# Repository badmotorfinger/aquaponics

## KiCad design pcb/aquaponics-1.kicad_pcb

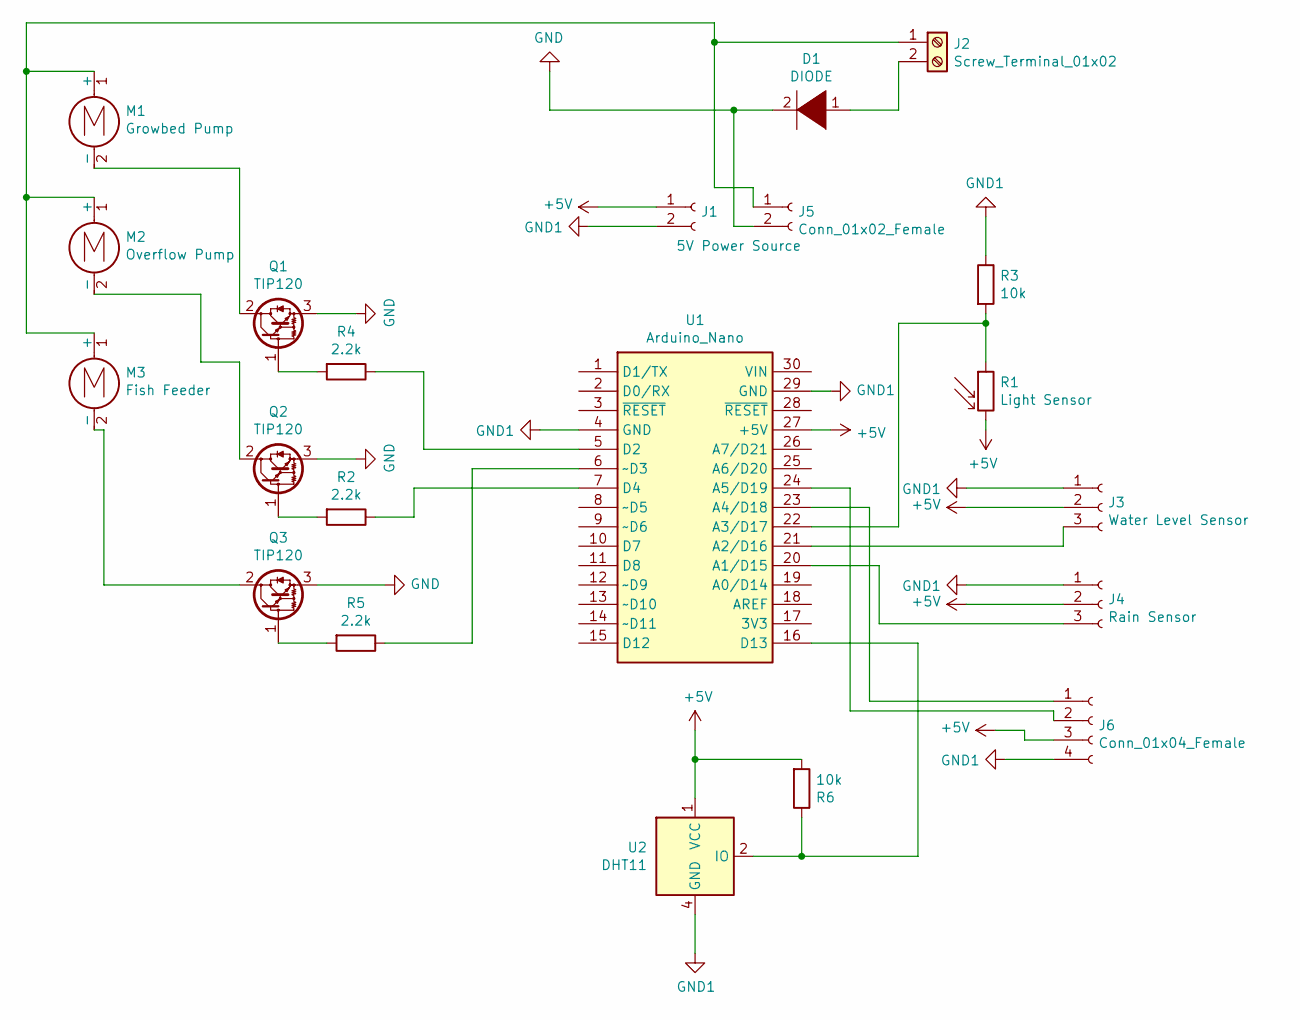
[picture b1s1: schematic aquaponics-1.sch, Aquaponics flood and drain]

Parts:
D1: DIODE; D_DO-15_P2.54mm_Vertical_AnodeUp
J1: 5V Power Source; VP-TE_826576-2_1x02_P3.96mm_Vertical
J2: Screw_Terminal_01x02; TerminalBlock_Phoenix_PT-1,5-2-5.0-H_1x02_P5.00mm_Horizontal
J3: Water Level Sensor; PinHeader_1x03_P2.54mm_Vertical
J4: Rain Sensor; PinHeader_1x03_P2.54mm_Vertical
J5: Conn_01x02_Female; VP-TE_826576-2_1x02_P3.96mm_Vertical
J6: Conn_01x04_Female; PinHeader_1x04_P2.54mm_Vertical
M1: Growbed Pump; PinHeader_1x02_P2.54mm_Vertical
M2: Overflow Pump; PinHeader_1x02_P2.54mm_Vertical
M3: Fish Feeder; PinHeader_1x02_P2.54mm_Vertical
Q1, Q2, Q3: TIP120; TO-220-3_Vertical
R1: Light Sensor; PinHeader_1x02_P2.54mm_Vertical
R2, R4, R5: 2.2k; R_Axial_DIN0204_L3.6mm_D1.6mm_P1.90mm_Vertical
R3, R6: 10k; R_Axial_DIN0204_L3.6mm_D1.6mm_P1.90mm_Vertical
U1: Arduino_Nano
U2: DHT11; Aosong_DHT11_5.5x12.0_P2.54mm

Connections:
+5V: J1.1, J3.2, J4.2, J6.3, R1.2, R6.2, U1.27 (+5V), U2.1 (VCC)
GND: D1.2 (A), J5.2, Q1.3 (E), Q2.3 (E), Q3.3 (E)
GND1: J1.2, J3.1, J4.1, J6.4, R3.1, U1.4 (GND), U1.29 (GND), U2.4 (GND)
unnamed: D1.1 (K), J2.2
unnamed: J2.1, J5.1, M1.1 (+), M2.1 (+), M3.1 (+)
unnamed: J3.3, U1.21 (A2/D16)
unnamed: J4.3, U1.20 (A1/D15)
unnamed: J6.1, U1.23 (A4/D18)
unnamed: J6.2, U1.24 (A5/D19)
unnamed: M1.2 (-), Q1.2 (C)
unnamed: M2.2 (-), Q2.2 (C)
unnamed: M3.2 (-), Q3.2 (C)
unnamed: Q1.1 (B), R4.2
unnamed: Q2.1 (B), R2.2
unnamed: Q3.1 (B), R5.2
unnamed: R1.1, R3.2, U1.22 (A3/D17)
unnamed: R2.1, U1.7 (D4)
unnamed: R4.1, U1.5 (D2)
unnamed: R5.1, U1.6 (~~D3)
unnamed: R6.1, U1.16 (D13), U2.2 (IO)

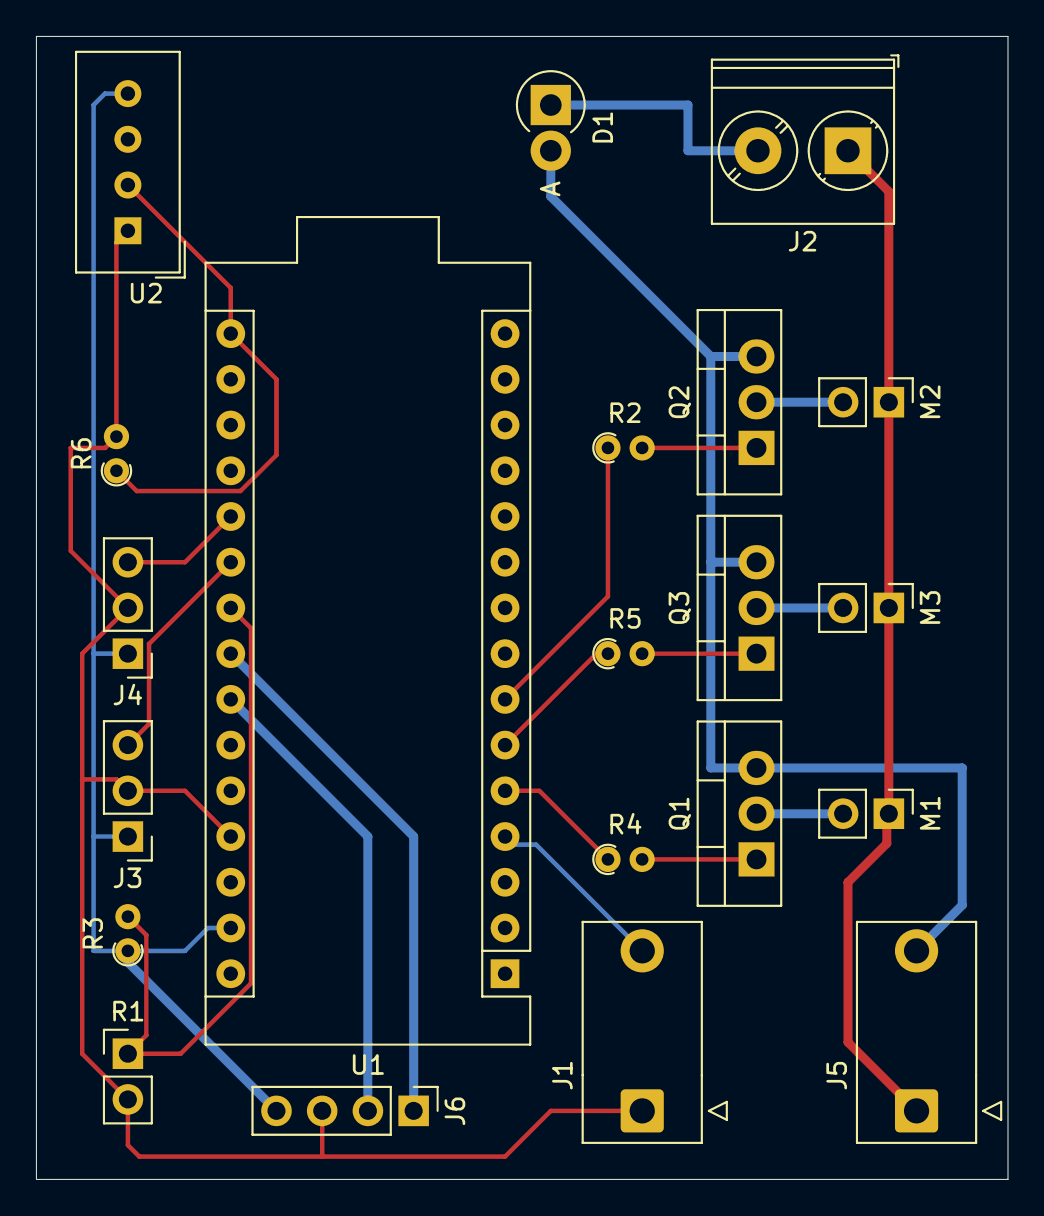
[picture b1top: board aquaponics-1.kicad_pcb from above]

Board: 2 copper layers, 54.0 x 63.5 mm, 21 parts (0 on the bottom side), 20 nets.

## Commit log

2021-12-05 A horrible first attempt at a PCB design
2021-12-15 Night time pump off to 60 minutes
2021-12-16 1st draft
2021-12-18 Update PCB'
2021-12-18 Change detection to water drain
2021-12-18 Remove
2021-12-18 KiCad ignore
2021-12-18 Only commit required files
2021-12-18 Ignore files
2021-12-18 Move files around
2021-12-23 Remove vscode from source control
2021-12-23 Update gitignore
2021-12-26 Update PCB /
2022-01-03 Changes after initial circuit print
2022-01-12 Version 2 board
2022-01-21 WIP: Using C++ classes
2022-01-22 Add WIP 3D housing for circuit
2022-01-27 Update PCB model
2022-01-27 Remove files which do not need to be checked in
2022-01-29 WIP: New code base
2022-01-30 Temp sensor to use 5V souce
2022-01-30 Temp sensor to use 5V power
2022-02-04 Incorporate LCD and separate sensors into classes
